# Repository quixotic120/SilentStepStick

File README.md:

# fork of SilentStepStick
The Silent-Step-Stick is a Stepper Motor Driver Board based on a [Trinamic TMC 2100](http://www.trinamic.com/products/integrated-circuits/stepper-power-driver/tmc2100) or [Trinamic TMC 2130](http://www.trinamic.com/products/integrated-circuits/stepper-power-driver/tmc2130).
The driver boards are hardware compatible with [StepStick](http://reprap.org/wiki/StepStick) and [Pololu A4988](https://www.pololu.com/product/1182).

## Shop
* Trinamic **TMC2100** based drivers (CFG pins for configuration)
  * [TMC2100 SilentStepStick (3.3-5V logic voltage)](http://www.watterott.com/en/SilentStepStick)
  * [TMC2100 SilentStepStick (3.3-5V logic voltage) with soldered Pin Headers](http://www.watterott.com/en/SilentStepStick-with-Pins)
  * [TMC2100 SilentStepStick (5V logic voltage)](http://www.watterott.com/en/SilentStepStick-TMC2100-5V)
  * [TMC2100 SilentStepStick (5V logic voltage) with soldered Pin Headers](http://www.watterott.com/en/SilentStepStick-TMC2100-5V-with-Pins)
* Trinamic **TMC2130** based drivers (SPI for configuration)
  * [TMC2130 SilentStepStick (3.3-5V logic voltage)](http://www.watterott.com/en/SilentStepStick-TMC2130)
* Accessories
  * [SilentStepStick Protector (with flyback diodes)](http://www.watterott.com/en/SilentStepStick-Protector)
  * [Suitable Heatsink 10x10mm](http://www.watterott.com/en/Pin-heatsink-square-ICK-S-10-x-10-x-125)
  * [Suitable Heatsink 10x6mm](http://www.watterott.com/en/Heatsink-for-DIL-IC-PLCC-und-SMD-10-x-6-mm)
  * [Suitable Heatsink 8x6mm](http://www.watterott.com/en/Heatsinks-6-3x8mm)

## Features
* Hardware compatible with [StepStick](http://reprap.org/wiki/StepStick) and [Pololu A4988](https://www.pololu.com/product/1182)
* Trinamic TMC21x0 stepper motor driver
* Step/Dir interface with up to 16 microsteps and 256 microsteps interpolation
* Motor current: up to **1.2A RMS** continuously and 2.5A short time peak current per coil
* Motor voltage: **5.5...45V** (3.3...5V logic) or **4.75...45V** (5V logic)
* **microPlyer** - microstep interpolator for increased smoothness of microstepping
* **stealthChop** - for quiet operation and smooth motion
* **spreadCycle** - highly dynamic motor control chopper
* Extra features of **TMC2130**:
  * SPI configuration interface (up to 4MHz)
  * up to 256 native microsteps (without interpolation)
  * **coolStep** - current control for energy savings
  * **stallGuard** - sensorless motor load detection
  * **dcStep** - load dependent speed control

## Hardware
* [Schematics/Layout + Guide](https://github.com/watterott/SilentStepStick/tree/master/hardware)
* [FAQ (Frequently Asked Questions)](https://github.com/watterott/SilentStepStick/blob/master/docu/FAQ.md)
* [Eagle CAD Part](https://github.com/watterott/Eagle-Libs)

## Reviews and Tests

* Review from Thomas Sanladerer:

* Review from Peter Recktenwald:

* Review from Georg Mill:

* What is Trinamic stallGuard2 and coolStep:

* Tests:
  * [Watterott (Stepper Motor)](https://www.youtube.com/watch?v=0l-HlntFYOY)
  * [Aleks (RepRap Prusa i3)](https://www.youtube.com/watch?v=33jQ0P7SMJA)
  * [Anthony (Delta Printer)](https://www.youtube.com/watch?v=CZOV0BdgSiU)
  * [Mario Lukas](https://www.youtube.com/watch?v=mJmg0iRHX8s)
  * Yusuke Sasaki: [TMC2100 steahlChop](https://www.youtube.com/watch?v=wrS7l46YJ_E), [TMC2100 spreadCycle](https://www.youtube.com/watch?v=391TY72wzPQ), [A4988](https://www.youtube.com/watch?v=iw6MRjzS6V4)
  * [MakerSpatz (Ultimaker)](https://www.youtube.com/watch?v=0jPbzB7XtWg)
  * [Aitor Esteve Alvarado (Ninja Prusa i3)](https://www.youtube.com/watch?v=c_TCVirnKJ0)
  * [Artur Wronowski (Delta Printer)](https://www.youtube.com/watch?v=hH2UkAmbfYs)
  * [3D Huynh (Felix 3D)](https://www.youtube.com/watch?v=EglFOpTXPtg)
  * [Easy 3D (Sparkcube)](https://www.youtube.com/watch?v=BxE_F8_Ec8M)
  * [WOLF HSW (linear drive)](https://www.youtube.com/watch?v=wjuAu0WYOPM)
  * Clarence Lee (ATOM Delta Printer): [TMC2100](https://www.youtube.com/watch?v=sBVNqFybUZI), [DRV8825](https://www.youtube.com/watch?v=tNufJnybsxg), [A4982](https://www.youtube.com/watch?v=r1noUt2UoO8)
  * Alex Tien (3DP Delta Printer): [TMC2100](https://www.youtube.com/watch?v=RcqnXXp4tPA), [A4988](https://www.youtube.com/watch?v=F2oB_NOLxHU)
  * swdjojo (Prusa i3): [TMC2100](https://www.youtube.com/watch?v=vBRNifmHaZE), [A4988](https://www.youtube.com/watch?v=TCgErVx93OA)
  * [Doc. Snuggles (Stepper Motor)](https://www.youtube.com/watch?v=gj6f6HSrHc4)
  * [Robert Sertic (Ultimaker)](https://www.youtube.com/watch?v=1wQJZb0gzoE)
  * [Emanuel Kant (Ultimaker)](https://www.youtube.com/watch?v=Y7CG43yf9zA)
  * [ghicione (EggBot)](https://www.youtube.com/watch?v=4FBAAQXnESU)
  * Edward Kuo: [E3D Cyclops Delta Printer](https://www.youtube.com/watch?v=iEYdrMH69oo), [TMC2100 water cooled](https://www.youtube.com/watch?v=vjNM9R0NZG0)
  * [Noah Ahmad Connor (Prusa i3)](https://www.youtube.com/watch?v=mNdl3s8TYmY)
  * [Sterillium (XYZ DaVinci)](https://www.youtube.com/watch?v=k-szP5wuplM)
  * [markg21405 (Delta Printer)](https://www.youtube.com/watch?v=tytL3KeIlLw)
  * [JJiG (MakerFarm Pegasus)](https://www.youtube.com/watch?v=9Rny6n1MCfI)
  * [René Jurack (Skimmy v3)](https://www.youtube.com/watch?v=qpl8v0k1_34)
  * [David Spaulding (A4988 vs. TMC2100)](https://www.youtube.com/watch?v=Z5OQpMSvWvs)
  * [Tarjeik (DRV8825 vs. TMC2100)](https://www.youtube.com/watch?v=oNAHOOolHWw)

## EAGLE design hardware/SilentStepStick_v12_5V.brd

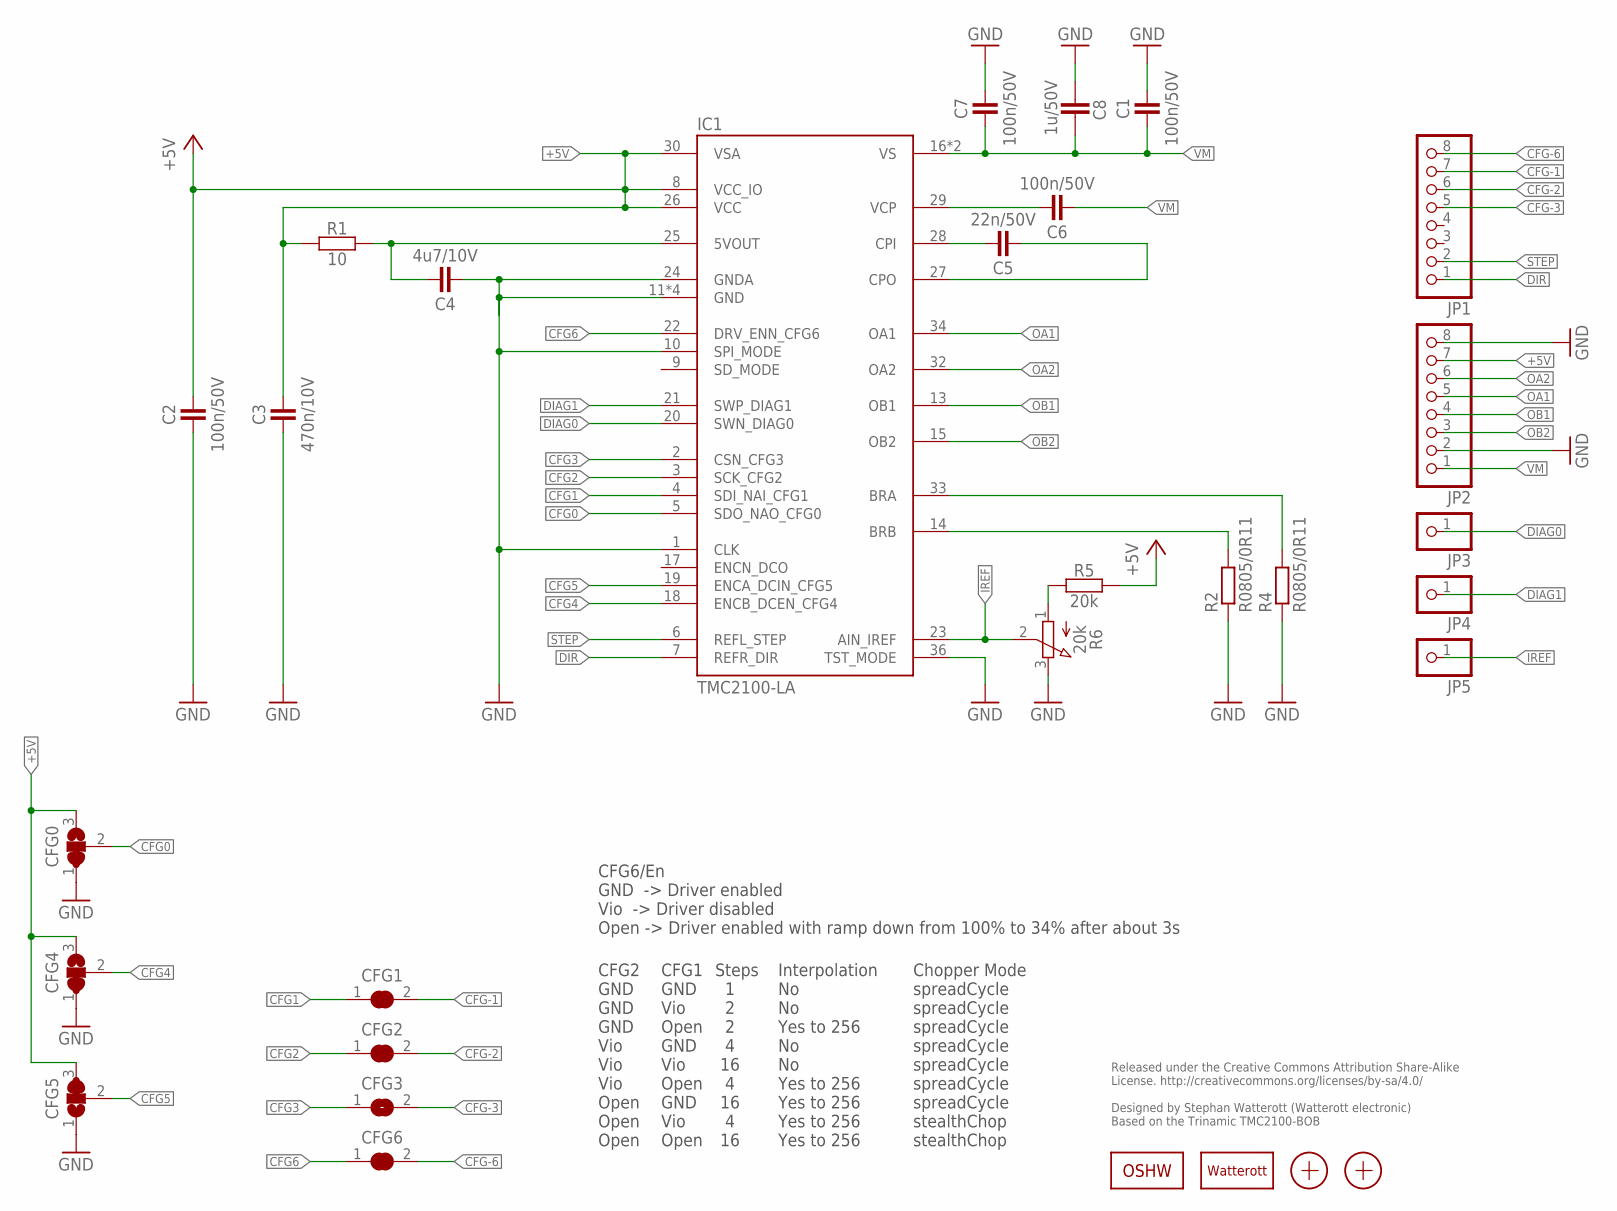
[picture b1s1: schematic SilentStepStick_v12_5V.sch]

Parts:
C1, C2, C6, C7: 100n/50V; C0402
C3: 470n/10V; C0402
C4: 4u7/10V; C0402
C5: 22n/50V; C0402
C8: 1u/50V; C0603
CFG0, CFG4, CFG5: JUMPER3-0201
CFG1, CFG2, CFG3, CFG6: JUMPER2-0201
IC1: TMC2100-LA; QFN36-PAD
JP1, JP2: PINHD-1X08_2.54-S; 1X08-S
JP3, JP4, JP5: PINHD-1X1; 1X01
LOGO1: OSHW_LOGOX0070; OSHW_6X70
LOGO2: LOGO-S_PLACE_M; SPARK_TPLACE_M
R1: 10; C0402
R2, R4: R0805/0R11; M0805
R5: 20k; C0402
R6: 20k; POT_EVM3R
X1, X2: PASSER-07; PASSER_07MM

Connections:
5VOUT: C4.2, IC1.25 (5VOUT), R1.2
+5V: C2.2, C3.2, CFG0.3, CFG4.3, CFG5.3, IC1.8 (VCC_IO), IC1.26 (VCC), IC1.30 (VSA), JP2.7, R1.1, R5.2
BRA: IC1.33 (BRA), R4.2
BRB: IC1.14 (BRB), R2.2
CFG0: CFG0.2, IC1.5 (SDO_NAO_CFG0)
CFG1: CFG1.1, IC1.4 (SDI_NAI_CFG1)
CFG2: CFG2.1, IC1.3 (SCK_CFG2)
CFG3: CFG3.1, IC1.2 (CSN_CFG3)
CFG4: CFG4.2, IC1.18 (ENCB_DCEN_CFG4)
CFG5: CFG5.2, IC1.19 (ENCA_DCIN_CFG5)
CFG6: CFG6.1, IC1.22 (DRV_ENN_CFG6)
CFG-1: CFG1.2, JP1.7
CFG-2: CFG2.2, JP1.6
CFG-3: CFG3.2, JP1.5
CFG-6: CFG6.2, JP1.8
CPI: C5.2, IC1.28 (CPI)
CPO: C5.1, IC1.27 (CPO)
DIAG0: IC1.20 (SWN_DIAG0), JP3.1
DIAG1: IC1.21 (SWP_DIAG1), JP4.1
DIR: IC1.7 (REFR_DIR), JP1.1
GND: C1.2, C2.1, C3.1, C4.1, C7.2, C8.2, CFG0.1, CFG4.1, CFG5.1, IC1.1 (CLK), IC1.10 (SPI_MODE), IC1.11 (GND), IC1.12 (GND), IC1.24 (GNDA), IC1.35 (GND), IC1.36 (TST_MODE), IC1.TP (GND), JP2.2, JP2.8, R2.1, R4.1, R6.3 (E)
IREF: IC1.23 (AIN_IREF), JP5.1, R6.2 (S)
OA1: IC1.34 (OA1), JP2.5
OA2: IC1.32 (OA2), JP2.6
OB1: IC1.13 (OB1), JP2.4
OB2: IC1.15 (OB2), JP2.3
STEP: IC1.6 (REFL_STEP), JP1.2
VCP: C6.2, IC1.29 (VCP)
VM: C1.1, C6.1, C7.1, C8.1, IC1.16 (VS), IC1.31 (VS), JP2.1
VREF1: R5.1, R6.1 (A)

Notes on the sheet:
Released under the Creative Commons Attribution Share-Alike License. http://creativecommons.org/licenses/by-sa/4.0/ Designed by Stephan Watterott (Watterott electronic) Based on the Trinamic TMC2100-BOB
CFG6/En GND -> Driver enabled Vio -> Driver disabled Open -> Driver enabled with ramp down from 100% to 34% after about 3s
CFG2 GND GND GND Vio Vio Vio Open Open Open
CFG1 GND Vio Open GND Vio Open GND Vio Open
Steps 1 2 2 4 16 4 16 4 16
Interpolation No No Yes to 256 No No Yes to 256 Yes to 256 Yes to 256 Yes to 256
Chopper Mode spreadCycle spreadCycle spreadCycle spreadCycle spreadCycle spreadCycle spreadCycle stealthChop stealthChop

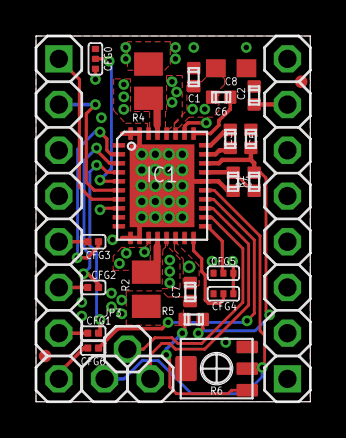
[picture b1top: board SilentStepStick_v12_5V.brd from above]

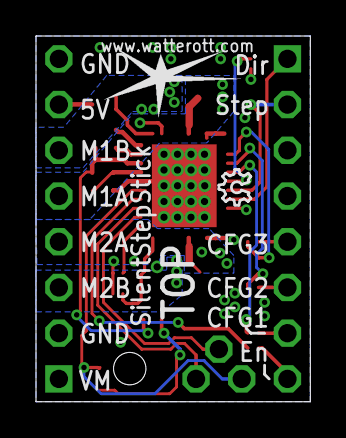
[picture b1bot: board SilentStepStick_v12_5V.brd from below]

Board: 4 copper layers, 15.2 x 20.3 mm, 30 parts (2 on the bottom side), 30 nets.

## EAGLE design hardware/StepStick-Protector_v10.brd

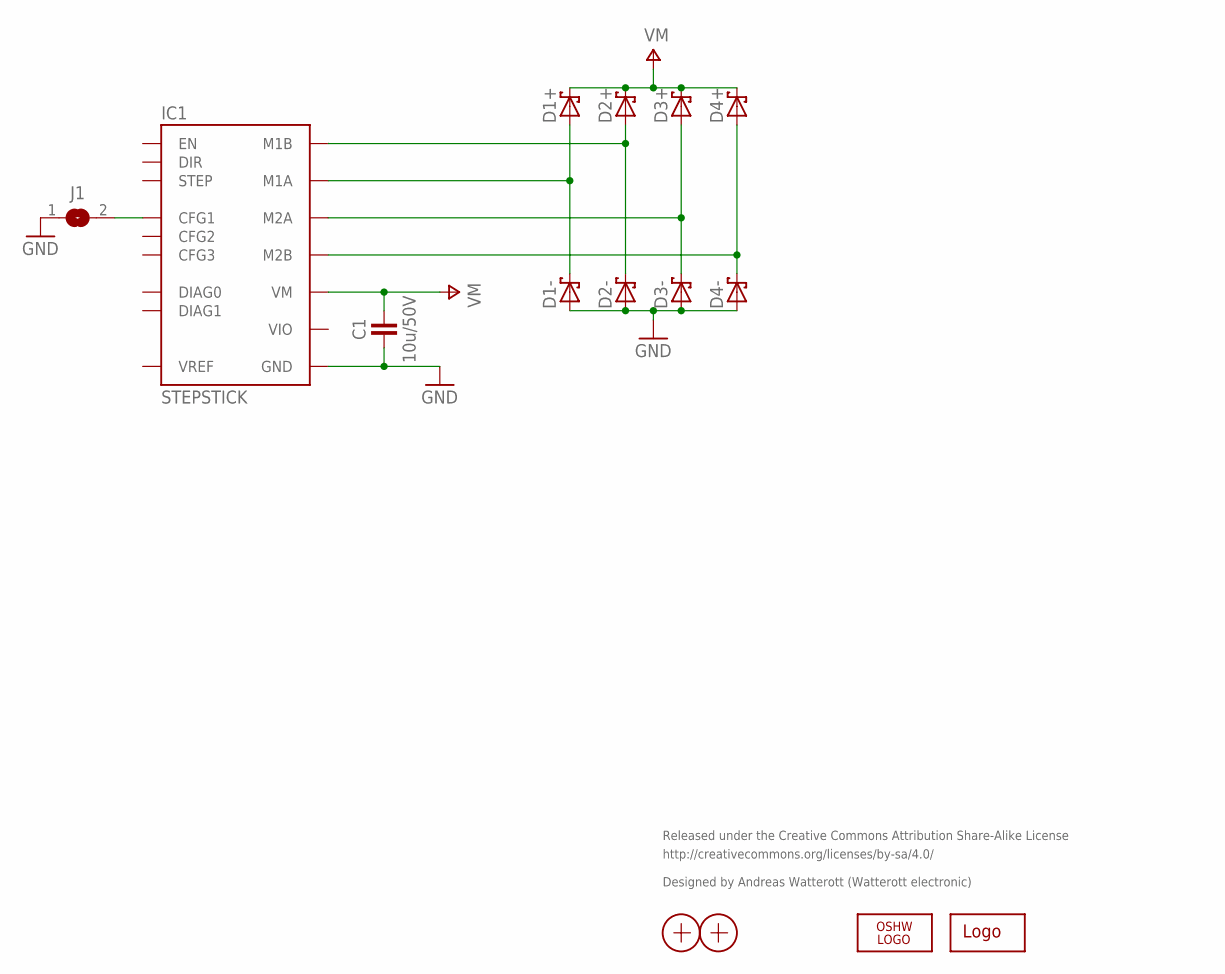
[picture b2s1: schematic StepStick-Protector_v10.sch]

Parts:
C1: 10u/50V; C1210
D1+, D1-, D2+, D2-, D3+, D3-, D4+, D4-: D_SCHOTTKY-SS14; SMA_DO214AC
IC1: STEPSTICK
J1: JUMPER2-0603-NC; JUMPER2-0603_NC
LOGO1: OSHW_LOGOX0070; OSHW_6X70
LOGO2: LOGO-S_PLACE_S; SPARK_TPLACE_S
X1, X2: PASSER

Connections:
GND: C1.1, D1-.A, D2-.A, D3-.A, D4-.A, IC1.GND@1 (GND), IC1.GND@2 (GND), J1.1
M1A: D1+.A, D1-.C, IC1.M1A
M1B: D2+.A, D2-.C, IC1.M1B
M2A: D3+.A, D3-.C, IC1.M2A
M2B: D4+.A, D4-.C, IC1.M2B
unnamed: IC1.CFG1, J1.2
VIO: IC1.VIO
VM: C1.2, D1+.C, D2+.C, D3+.C, D4+.C, IC1.VM

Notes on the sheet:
Released under the Creative Commons Attribution Share-Alike License
http://creativecommons.org/licenses/by-sa/4.0/
Designed by Andreas Watterott (Watterott electronic)

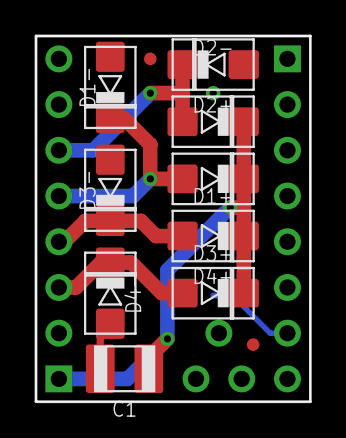
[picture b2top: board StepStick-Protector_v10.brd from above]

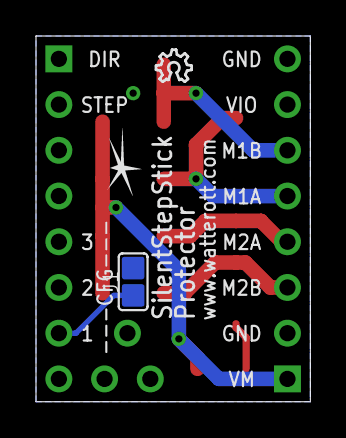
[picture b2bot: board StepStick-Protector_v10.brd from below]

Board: 2 copper layers, 15.2 x 20.3 mm, 15 parts (3 on the bottom side), 7 nets.

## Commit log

2015-01-04 added readme
2015-01-20 added layout and schematics
2015-01-21 updated layout and schematics
2015-01-23 updated readme and docu
2015-01-28 updated schematics
2015-01-28 updated image
2015-02-03 updated docu
2015-02-10 added small guide
2015-04-07 updated docu and readme
2015-05-05 added further infos
2015-08-21 changed path structure
2016-03-06 added TMC2130 example
2016-03-06 added TMC2130 layout and schematics
2016-03-09 updated examples
2016-04-26 updated example
2016-05-16 updated images
2016-07-19 added 5V TMC2100 SilentStepStick
